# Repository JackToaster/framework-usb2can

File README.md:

# framework CAN Interface

USB to CAN device that fits in a Framework laptop expansion card.

## Hardware

The USB to CAN device is based on the _STM32G431_ microcontroller and _TCAN1042_ CAN transceiver.

The hardware is inspired by (but not a direct clone of) the [Canable 2.0](https://canable.io/).

It includes a removeable push-in spring connector for easy wiring to any CAN bus.

## Software support

Supports CANFD (Up to 5Mbaud) with _slcan_ firmware, and socketcan on Linux with _candlelight_ firmware.

For software support, see the "_Software Support_" section at [canable.io](https://canable.io/)

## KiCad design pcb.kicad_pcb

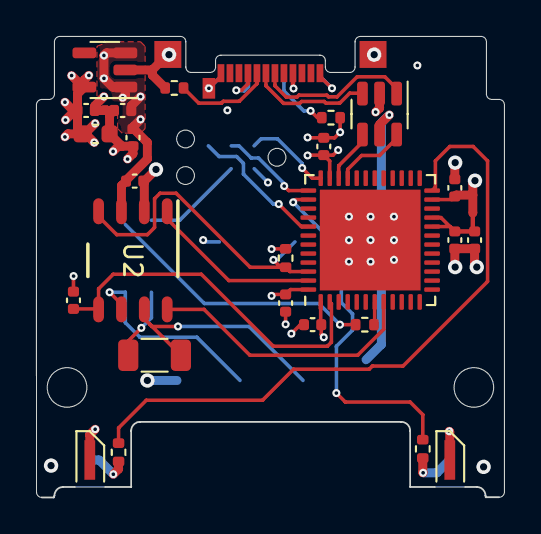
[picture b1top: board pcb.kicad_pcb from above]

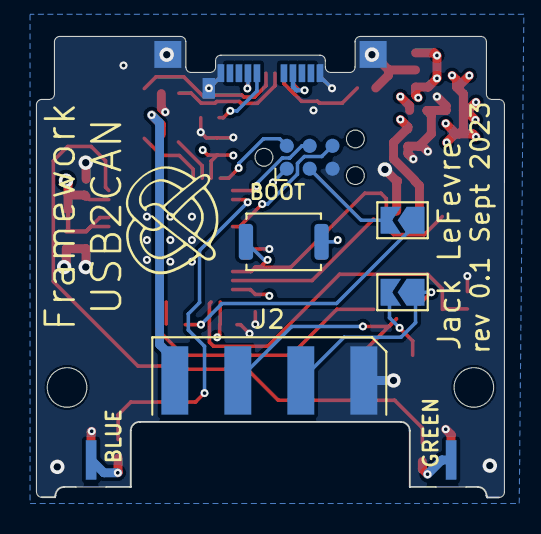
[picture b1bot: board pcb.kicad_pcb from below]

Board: 4 copper layers, 26.0 x 25.6 mm, 38 parts (7 on the bottom side), 27 nets.

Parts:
C1, C2, C4, C5, C6, C8, C10, C11: 100n; C_0402_1005Metric
C3: 4u7; C_0603_1608Metric
C9, C14, C15: 1u; C_0402_1005Metric
D2: Blue; LED_THT_Edge Mount
D3: Green; LED_THT_Edge Mount
H1, H2: MountingHole; MountingHole_2.2mm_M2
J1: TC2030-NL; Tag-Connect_TC2030-IDC-NL_2x03_P1.27mm_Vertical
J2: Conn_01x04; p3_5_edge_header
JP1: TERM; SolderJumper-2_P1.3mm_Open_TrianglePad1.0x1.5mm
JP2: RESET; SolderJumper-2_P1.3mm_Open_TrianglePad1.0x1.5mm
NT1: NetTie_2; NetTie-2_SMD_Pad0.5mm
P1: USB_C_Plug; USB_C_Plug_Molex_105444
R1, R2: 5.1k; R_0402_1005Metric
R3: 220k; R_0402_1005Metric
R4: 120; R_1206_3216Metric
R5, R9, R10: 330R; R_0402_1005Metric
SW1: BOOT; SW_Push_SPST_NO_Alps_SKRK
TP1, TP2, TP3, TP4: TestPoint; TestPoint_Pad_1.5x1.5mm
U1: WE-TVS-82400102; SOT-23-6
U2: TCAN1042HGVDQ1; D0008A_N
U3: STM32G431CBUx; QFN-48-1EP_7x7mm_P0.5mm_EP5.6x5.6mm
U9: AP2112K-3.3; SOT-23-5

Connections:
+3V3: C3.1, C4.1, C5.1, C6.1, C8.1, C15.1, J1.1 (VCC), NT1.1, SW1.1, U3.1 (VBAT), U3.23 (VDD), U3.35 (VDD), U3.48 (VDD), U9.5 (VOUT)
/SSD+: P1.A6 (D+), U1.3
/SSD-: P1.A7 (D-), U1.1
CANRX: R3.1, SW1.2, U2.4 (RXD), U3.46 (PB8)
CANTX: U2.1 (TXD), U3.47 (PB9)
CAN_IOPWR: C1.1, U2.5 (VIO), U3.2 (PC13)
CAN_STBY: U2.8 (STB), U3.8 (PA0)
GND: C1.2, C2.2, C3.2, C4.2, C5.2, C6.2, C8.2, C9.2, C10.2, C11.2, C14.2, C15.2, D2.1 (K), D3.1 (K), J1.5 (GND), J2.1, P1.A1 (GND), P1.A12 (GND), P1.B1 (GND), P1.B12 (GND), P1.S1 (SHIELD), R1.2, R2.2, R3.2, TP1.1, TP2.1, TP3.1, TP4.1, U1.2, U2.2 (GND), U3.49 (VSS), U9.2 (GND)
LEDB: R9.1, U3.38 (PA15)
LEDG: R10.1, U3.24 (PB11)
unnamed: D2.2 (A), R9.2
unnamed: D3.2 (A), R10.2
unnamed: J2.2, JP1.1 (A), U2.6 (CANL)
unnamed: J2.3, R4.1, U2.7 (CANH)
unnamed: JP1.2 (B), R4.2
unnamed: JP2.1 (A), R5.1
unnamed: P1.A5 (CC), R1.1
unnamed: P1.B5 (VCONN), R2.1
unnamed: R5.2, U3.7 (PG10)
SWCLK: J1.4 (SWCLK), U3.37 (PA14)
SWDIO: J1.2 (SWDIO), U3.36 (PA13)
SWO: J1.6 (SWO), U3.41 (PB3)
USB_D+: U1.4, U3.34 (PA12)
USB_D-: U1.6, U3.33 (PA11)
VBUS: C2.1, C11.1, C14.1, J2.4, P1.A4 (VBUS), P1.A9 (VBUS), P1.B4 (VBUS), P1.B9 (VBUS), U1.5, U2.3 (VCC), U9.1 (VIN), U9.3 (EN)
VDDA: C9.1, C10.1, NT1.2, U3.20 (VREF+), U3.21 (VDDA)
nRESET: J1.3 (~RESET), JP2.2 (B)

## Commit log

2023-06-20 schematic done
2023-06-24 Shrinking
2023-06-25 Layout and routing
2023-06-25 part numbers
2023-06-25 move parts around
2023-06-25 update part numbers
2023-09-08 made usb2can schematic/pcb
2023-09-08 fixed erc
2023-09-08 clean up tracks/vias
2023-09-16 Add exclusion to DRC check
2023-09-16 Added renders
